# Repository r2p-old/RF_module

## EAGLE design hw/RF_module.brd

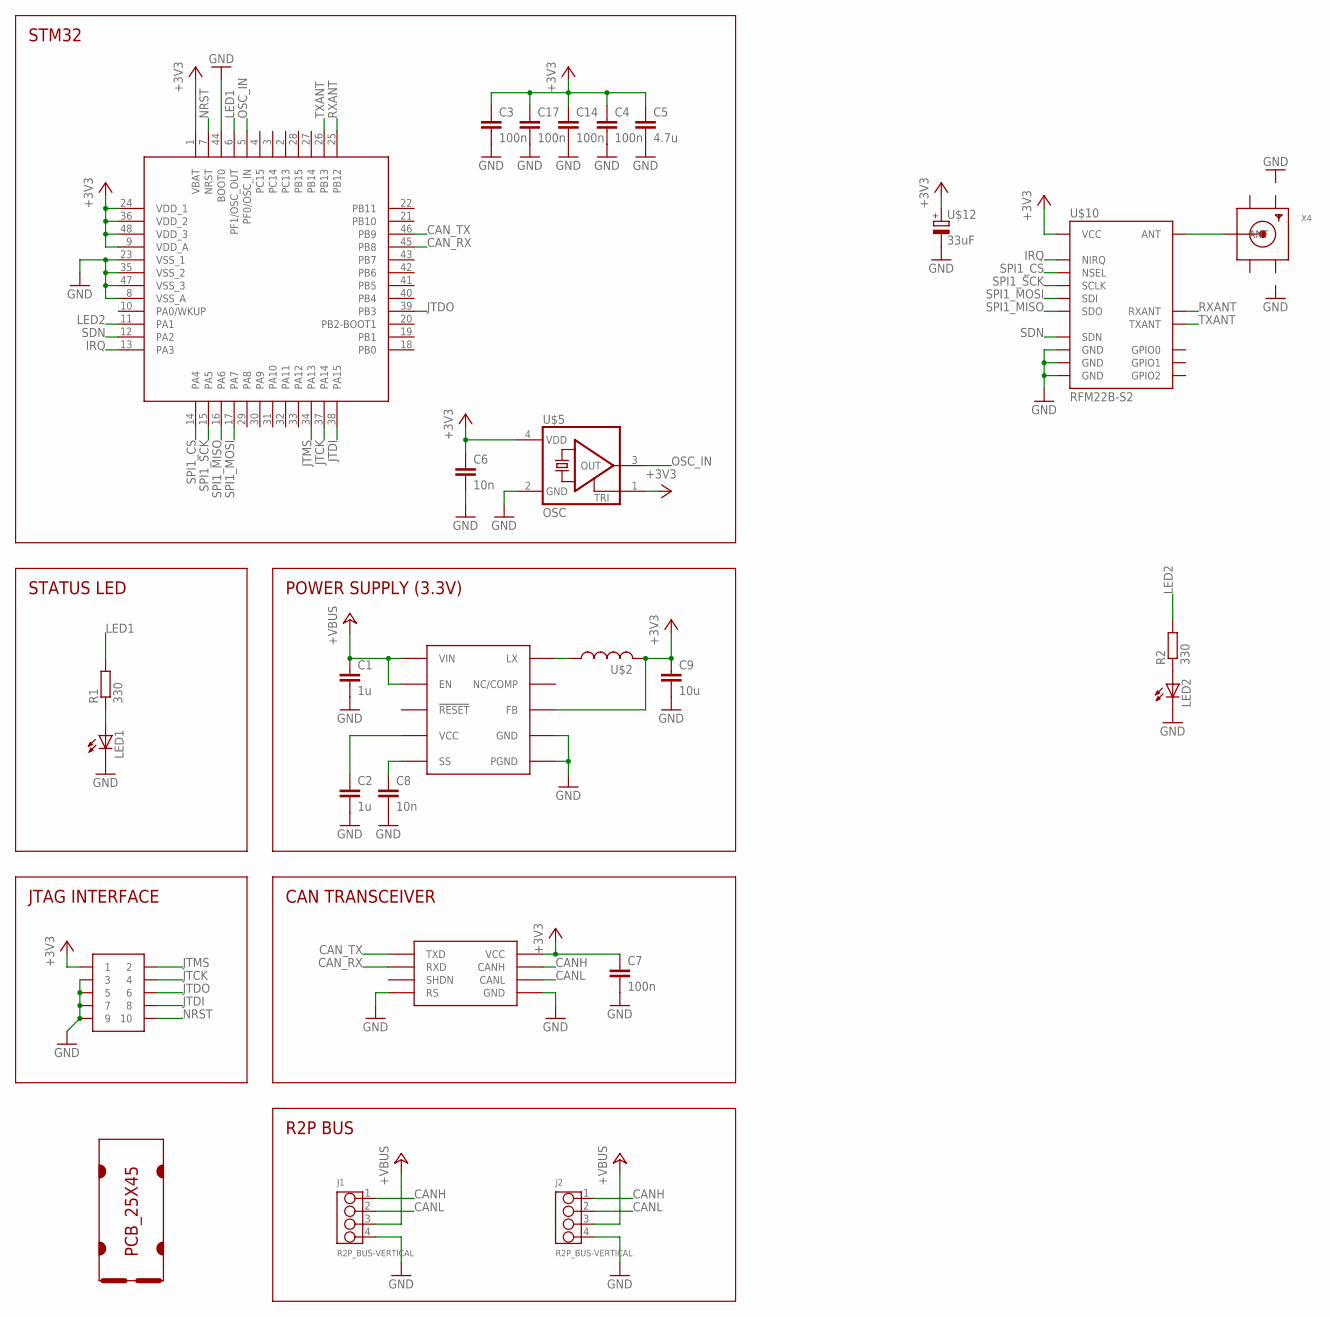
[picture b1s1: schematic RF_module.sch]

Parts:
C1: 1u; C1206
C2: 1u; C0603
C3, C4, C7, C14, C17: 100n; C0603
C5: 4.7u; C0805
C6, C8: 10n; C0603
C9: 10u; C0805
J1, J2: R2P_BUS-VERTICAL; OPL-EAGLE-LIBRARY_4P-2.0
LED1, LED2: LED0805; CHIPLED_0805
R1, R2: 330; R0603
SOT1: MAX3051EKA; SOT23-8L
U$1: PCB_25X45; 25X45
U$2: LPS4018; COILCRAFT_LPS4018
U$3: MAX17501; TDFN-10
U$4: JTAG-TH; SAMTEC_FTSH-105-TH
U$5: OSC; XTAL_2.5X2
U$6: STM32F303CTX; LQFP48
U$10: RFM22B-S2
U$12: 33uF; CPOL_B
X4: SMACONNECTOR_EDGE_UFL; SMA_EDGELAUNCH_UFL

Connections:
+3V3: C3.1, C4.1, C5.1, C6.1, C7.1, C9.1, C14.1, C17.1, SOT1.3 (VCC), U$2.P$2 (2), U$3.P$5 (FB), U$4.1, U$5.1 (TRI), U$5.4 (VDD), U$6.1 (VBAT), U$6.9 (VDD_A), U$6.24 (VDD_1), U$6.36 (VDD_2), U$6.48 (VDD_3), U$10.P$5 (VCC), U$12.+
+VBUS: C1.1, J1.3, J2.3, U$3.P$2 (VIN), U$3.P$3 (EN)
CANH: J1.1, J2.1, SOT1.7 (CANH)
CANL: J1.2, J2.2, SOT1.6 (CANL)
CAN_RX: SOT1.4 (RXD), U$6.45 (PB8)
CAN_TX: SOT1.1 (TXD), U$6.46 (PB9)
GND: C1.2, C2.2, C3.2, C4.2, C5.2, C6.2, C7.2, C8.2, C9.2, C14.2, C17.2, J1.4, J2.4, LED1.C, LED2.C, SOT1.2 (GND), SOT1.8 (RS), U$3.P$1 (PGND), U$3.P$9 (GND), U$3.P$11 (PGND), U$4.3, U$4.5, U$4.7, U$4.9, U$5.2 (GND), U$6.8 (VSS_A), U$6.23 (VSS_1), U$6.35 (VSS_2), U$6.44 (BOOT0), U$6.47 (VSS_3), U$10.P$2 (GND), U$10.P$9 (GND), U$10.P$16 (GND), U$12.-
GND1: X4.GND@1 (GND1)
GND2: X4.GND@2 (GND2)
GND3: X4.GND@3 (GND3)
GND4: X4.GND@4 (GND4)
IRQ: U$6.13 (PA3), U$10.P$14 (NIRQ)
JTCK: U$4.4, U$6.37 (PA14)
JTDI: U$4.8, U$6.38 (PA15)
JTDO: U$4.6, U$6.39 (PB3)
JTMS: U$4.2, U$6.34 (PA13)
LED1: R1.2, U$6.6 (PF1/OSC_OUT)
LED2: R2.2, U$6.11 (PA1)
unnamed: U$2.P$1 (1), U$3.P$10 (LX)
unnamed: LED2.A, R2.1
unnamed: LED1.A, R1.1
unnamed: U$10.P$1 (ANT), X4.P (ANT)
unnamed: C2.1, U$3.P$4 (VCC)
unnamed: C8.1, U$3.P$6 (SS)
NRST: U$4.10, U$6.7 (NRST)
OSC_IN: U$5.3 (OUT), U$6.5 (PF0/OSC_IN)
RXANT: U$6.25 (PB12), U$10.P$3 (RXANT)
SDN: U$6.12 (PA2), U$10.P$15 (SDN)
SPI1_CS: U$6.14 (PA4), U$10.P$13 (NSEL)
SPI1_MISO: U$6.16 (PA6), U$10.P$10 (SDO)
SPI1_MOSI: U$6.17 (PA7), U$10.P$11 (SDI)
SPI1_SCK: U$6.15 (PA5), U$10.P$12 (SCLK)
TXANT: U$6.26 (PB13), U$10.P$4 (TXANT)

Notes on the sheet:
STM32
STATUS LED
JTAG INTERFACE
POWER SUPPLY (3.3V)
CAN TRANSCEIVER
R2P BUS

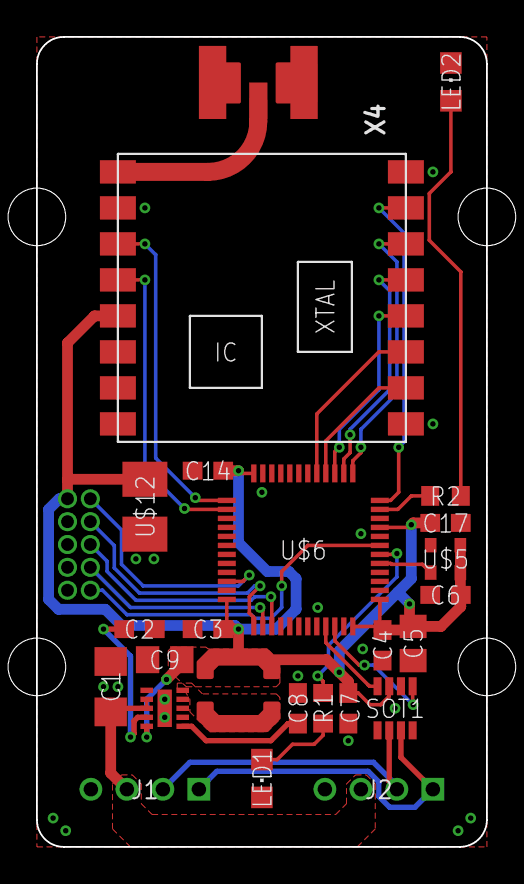
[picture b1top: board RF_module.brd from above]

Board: 2 copper layers, 25.0 x 45.0 mm, 27 parts (0 on the bottom side), 29 nets.

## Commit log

2015-02-08 Layout complete
2015-02-09 Updated keepout
2015-02-19 Fixed silkscreen
